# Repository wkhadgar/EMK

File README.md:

# EMK
EDGE Macro Keyboard using ZMK

# BOM
Link 1: https://docs.google.com/spreadsheets/d/1feDPUKi6qvB3Wog3a3WXaTfP1I-IvefD0QiZMtcDikI/edit?usp=sharing

Link 2: https://docs.google.com/spreadsheets/d/19HNuX7kSN2P8mtOWgADNLb8_vFuXl1ejLlQBJqbNmKw/edit?gid=1410846494#gid=1410846494

# Block Diagram:

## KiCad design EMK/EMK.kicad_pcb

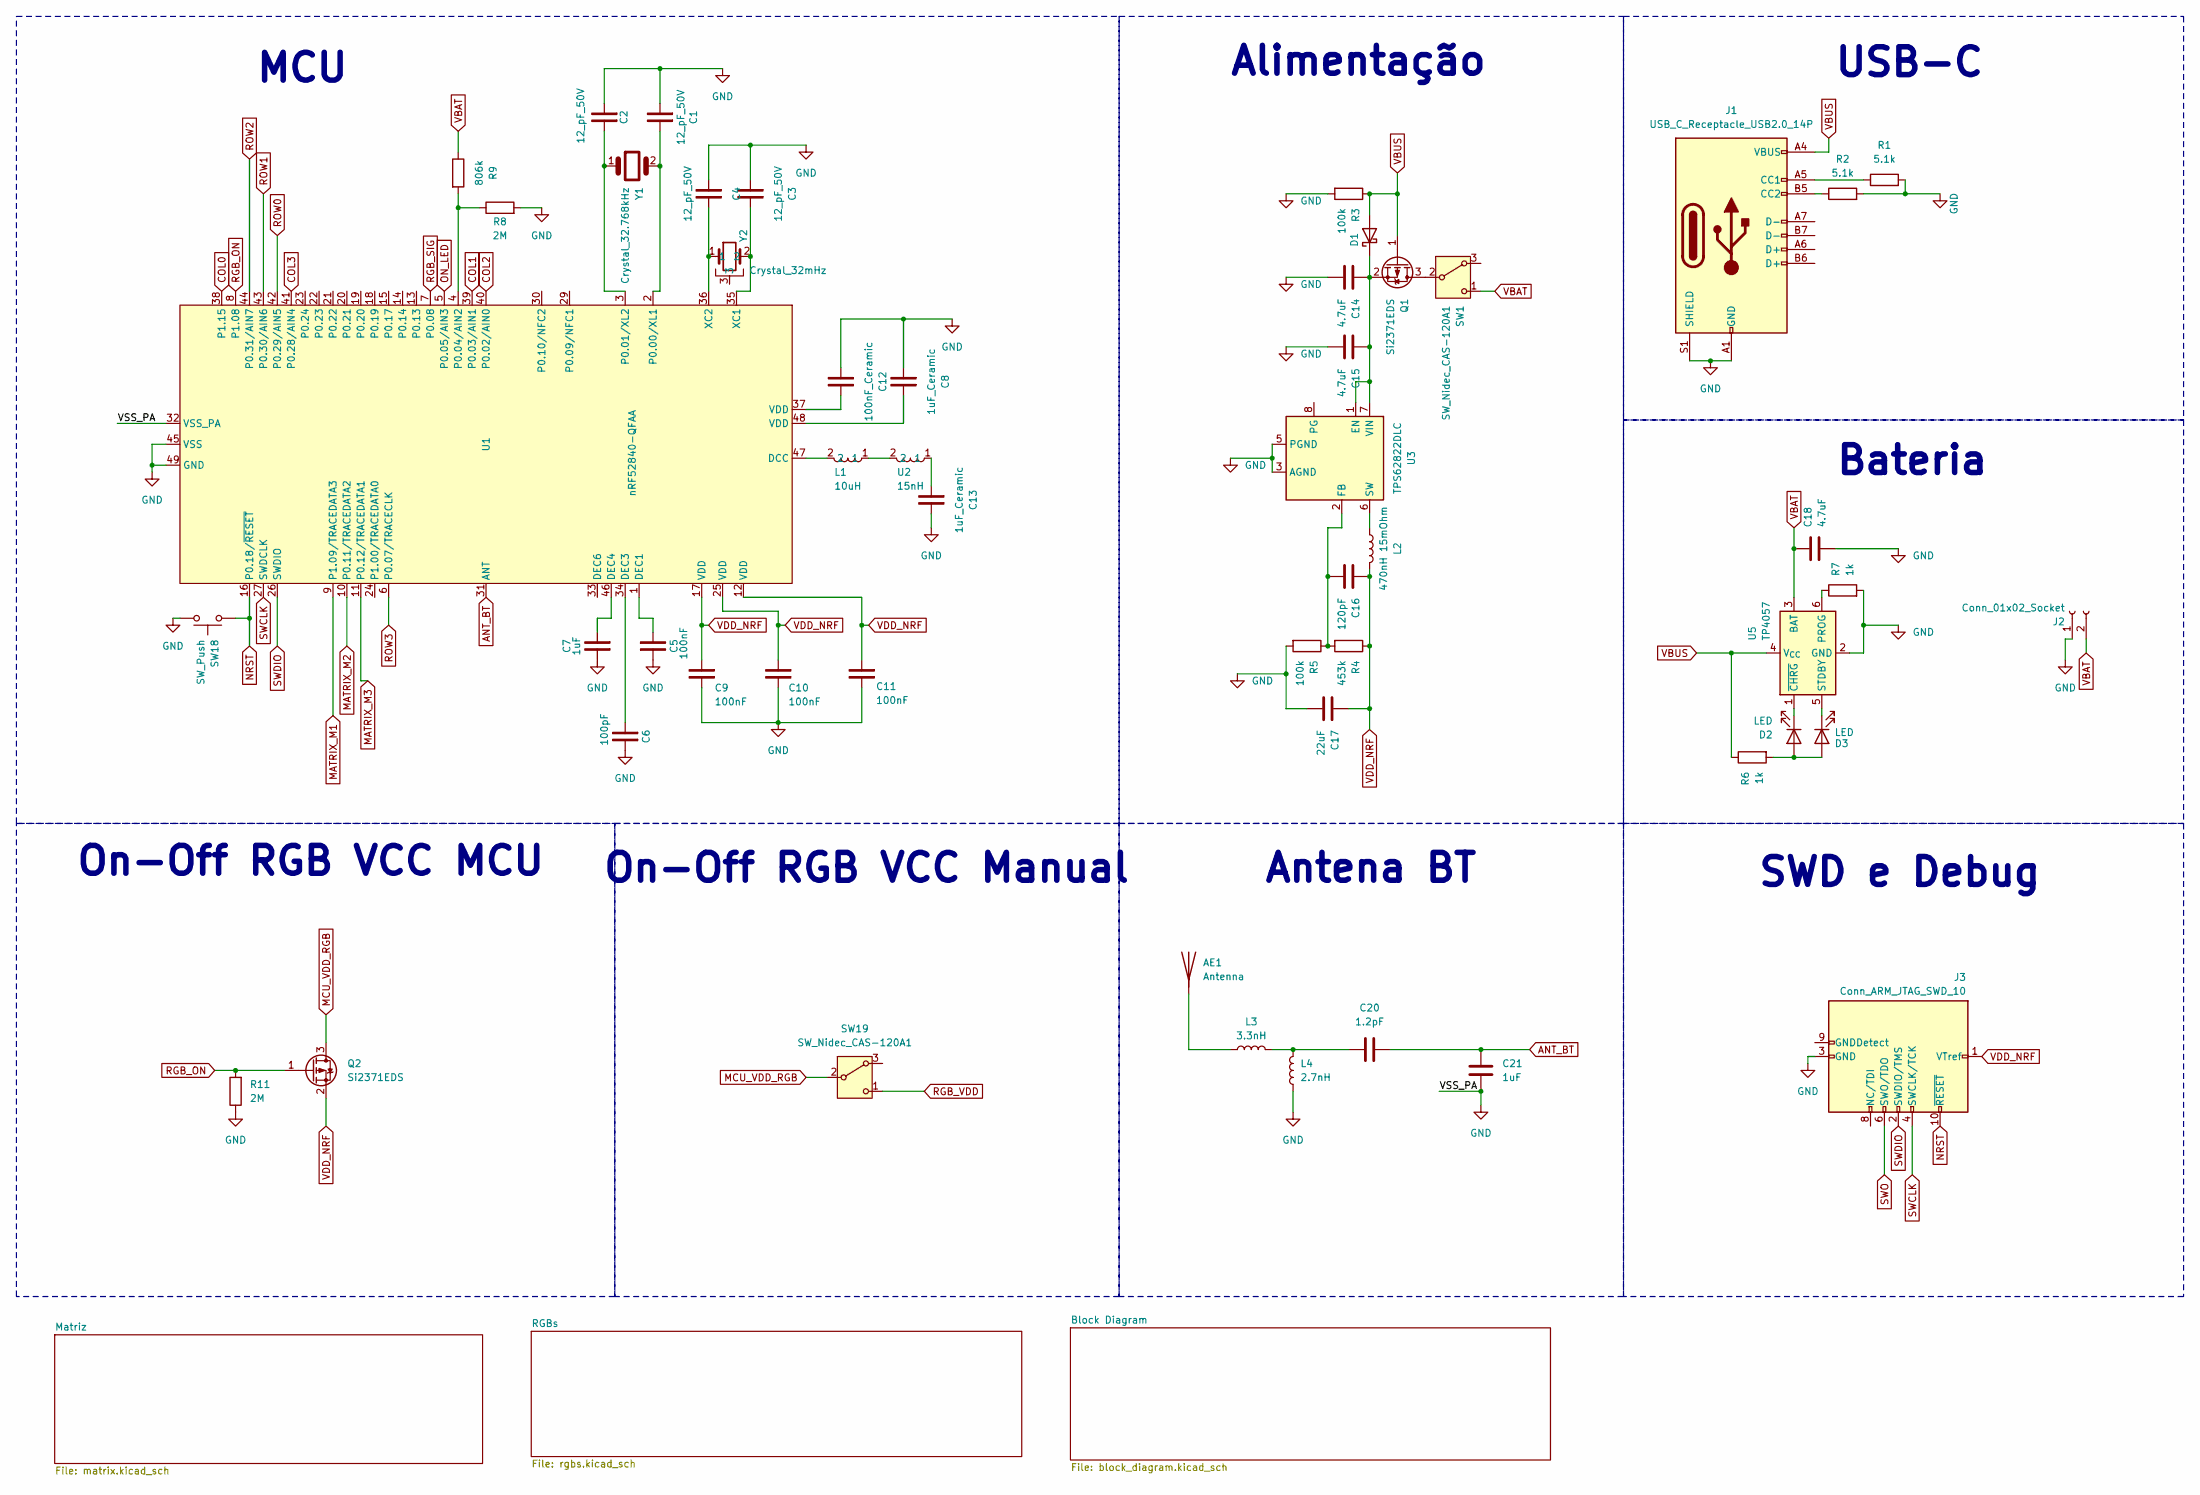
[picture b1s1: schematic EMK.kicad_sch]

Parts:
AE1: Antenna; Johanson_2450AT18x100
C1, C2, C3, C4: 12_pF_50V; C_0603_1608Metric
C5, C9, C10, C11: 100nF; C_0603_1608Metric
C6: 100pF; C_0603_1608Metric
C7: 1uF; C_0402_1005Metric
C8, C13: 1uF_Ceramic; C_0603_1608Metric
C12: 100nF_Ceramic; C_0603_1608Metric
C14, C15, C18: 4.7uF; C_0603_1608Metric
C16: 120pF; C_0603_1608Metric
C17: 22uF; C_0603_1608Metric
C20: 1.2pF; C_0402_1005Metric
C21: 1uF; C_0603_1608Metric
D1: D_Schottky; D_0805_2012Metric
D2, D3: LED; LED_0603_1608Metric
J1: USB_C_Receptacle_USB2.0_14P; USB_C_Receptacle_XKB_U262-16XN-4BVC11
J2: Conn_01x02_Socket; PinHeader_1x02_P2.54mm_Horizontal
J3: Conn_ARM_JTAG_SWD_10; ARM_SWD_SMD_TH
L1: 10uH; L_0603_1608Metric
L2: 470nH 15mOhm; L_7.3x7.3_H4.5
L3: 3.3nH; L_0402_1005Metric
L4: 2.7nH; L_0402_1005Metric_Pad0.77x0.64mm_HandSolder
Q1, Q2: Si2371EDS; SOT-23
R1, R2: 5.1k; R_0603_1608Metric
R3, R5: 100k; R_0603_1608Metric
R4: 453k; R_0603_1608Metric
R6, R7: 1k; R_0603_1608Metric
R8: 2M; R_0603_1608Metric
R9: 806k; R_0603_1608Metric
R11: 2M; R_0402_1005Metric
SW1, SW19: SW_Nidec_CAS-120A1; Nidec_Copal_CAS-120A
SW18: SW_Push; SW_SPST_B3U-1000P
U1: nRF52840-QFAA; QFN-48-1EP_6x6mm_P0.4mm_EP4.6x4.6mm
U2: 15nH; L_0603_1608Metric
U3: TPS62822DLC; Texas_VSON-HR-8_1.5x2mm_P0.5mm
U5: TP4057; TSOT-23-6
Y1: Crystal_32.768kHz; Crystal_SMD_2012-2Pin_2.0x1.2mm
Y2: Crystal_32mHz; Crystal_SMD_3215-2Pin_3.2x1.5mm

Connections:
ANT_BT: C20.2, C21.1, U1.31 (ANT)
COL0: U1.38 (P1.15); also elsewhere on the board
COL1: U1.39 (P0.03/AIN1); also elsewhere on the board
COL2: U1.40 (P0.02/AIN0); also elsewhere on the board
COL3: U1.41 (P0.28/AIN4); also elsewhere on the board
GND: C1.1, C2.1, C3.1, C4.1, C5.1, C6.2, C7.2, C8.1, C9.2, C10.2, C11.2, C12.1, C13.2, C14.2, C15.2, C17.2, C18.2, C21.2, J1.A1 (GND), J1.A12 (GND), J1.B1 (GND), J1.B12 (GND), J1.S1 (SHIELD), J2.1, J3.3 (GND), J3.5 (GND), L4.1, R1.2, R2.2, R3.2, R5.2, R7.2, R8.2, R11.1, SW18.2, U1.32 (VSS_PA), U1.45 (VSS), U1.49 (GND), U3.3 (AGND), U3.5 (PGND), U5.2 (GND); also elsewhere on the board
MATRIX_M1: U1.9 (P1.09/TRACEDATA3); also elsewhere on the board
MATRIX_M2: U1.10 (P0.11/TRACEDATA2); also elsewhere on the board
MATRIX_M3: U1.11 (P0.12/TRACEDATA1); also elsewhere on the board
MCU_VDD_RGB: Q2.3 (D), SW19.2 (B)
NRST: J3.10 (~RESET), SW18.1, U1.16 (P0.18/~RESET)
unnamed: AE1.1 (A), L3.1
unnamed: C8.2, U1.48 (VDD)
unnamed: C12.2, U1.37 (VDD)
unnamed: C13.1, U2.1
unnamed: C20.1, L3.2, L4.2
unnamed: C14.1, C15.1, D1.1 (K), Q1.2 (S), U3.1 (EN), U3.7 (VIN)
unnamed: D2.2 (A), D3.2 (A), R6.2
unnamed: D2.1 (K), U5.1 (~CHRG)
unnamed: D3.1 (K), U5.5 (STDBY)
unnamed: J1.A5 (CC1), R1.1
unnamed: J1.B5 (CC2), R2.1
unnamed: L1.1, U2.2
unnamed: Q1.3 (D), SW1.2 (B)
unnamed: L1.2, U1.47 (DCC)
unnamed: C5.2, U1.1 (DEC1)
unnamed: C6.1, U1.34 (DEC3)
unnamed: C7.1, U1.46 (DEC4)
unnamed: C1.2, U1.2 (P0.00/XL1), Y1.2
unnamed: C2.2, U1.3 (P0.01/XL2), Y1.1
unnamed: R8.1, R9.2, U1.4 (P0.04/AIN2)
unnamed: C3.2, U1.35 (XC1), Y2.2
unnamed: C4.2, U1.36 (XC2), Y2.1
unnamed: C16.2, R4.2, R5.1, U3.2 (FB)
unnamed: L2.1, U3.6 (SW)
unnamed: R7.1, U5.6 (PROG)
ON_LED: U1.5 (P0.05/AIN3); also elsewhere on the board
RGB_ON: Q2.1 (G), R11.2, U1.8 (P1.08)
RGB_SIG: U1.7 (P0.08); also elsewhere on the board
RGB_VDD: SW19.1 (C); also elsewhere on the board
ROW0: U1.42 (P0.29/AIN5); also elsewhere on the board
ROW1: U1.43 (P0.30/AIN6); also elsewhere on the board
ROW2: U1.44 (P0.31/AIN7); also elsewhere on the board
ROW3: U1.6 (P0.07/TRACECLK); also elsewhere on the board
SWCLK: J3.4 (SWCLK/TCK), U1.27 (SWDCLK)
SWDIO: J3.2 (SWDIO/TMS), U1.26 (SWDIO)
SWO: J3.6 (SWO/TDO)
VBAT: C18.1, J2.2, R9.1, SW1.1 (C), U5.3 (BAT)
VBUS: D1.2 (A), J1.A4 (VBUS), J1.A9 (VBUS), J1.B4 (VBUS), J1.B9 (VBUS), Q1.1 (G), R3.1, R6.1, U5.4 (V_{CC})
VDD_NRF: C9.1, C10.1, C11.1, C16.1, C17.1, J3.1 (VTref), L2.2, Q2.2 (S), R4.1, U1.12 (VDD), U1.17 (VDD), U1.25 (VDD); also elsewhere on the board

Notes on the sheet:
Alimentação
Bateria
SWD e Debug
MCU
Antena BT
On-Off RGB VCC MCU
On-Off RGB VCC Manual
USB-C

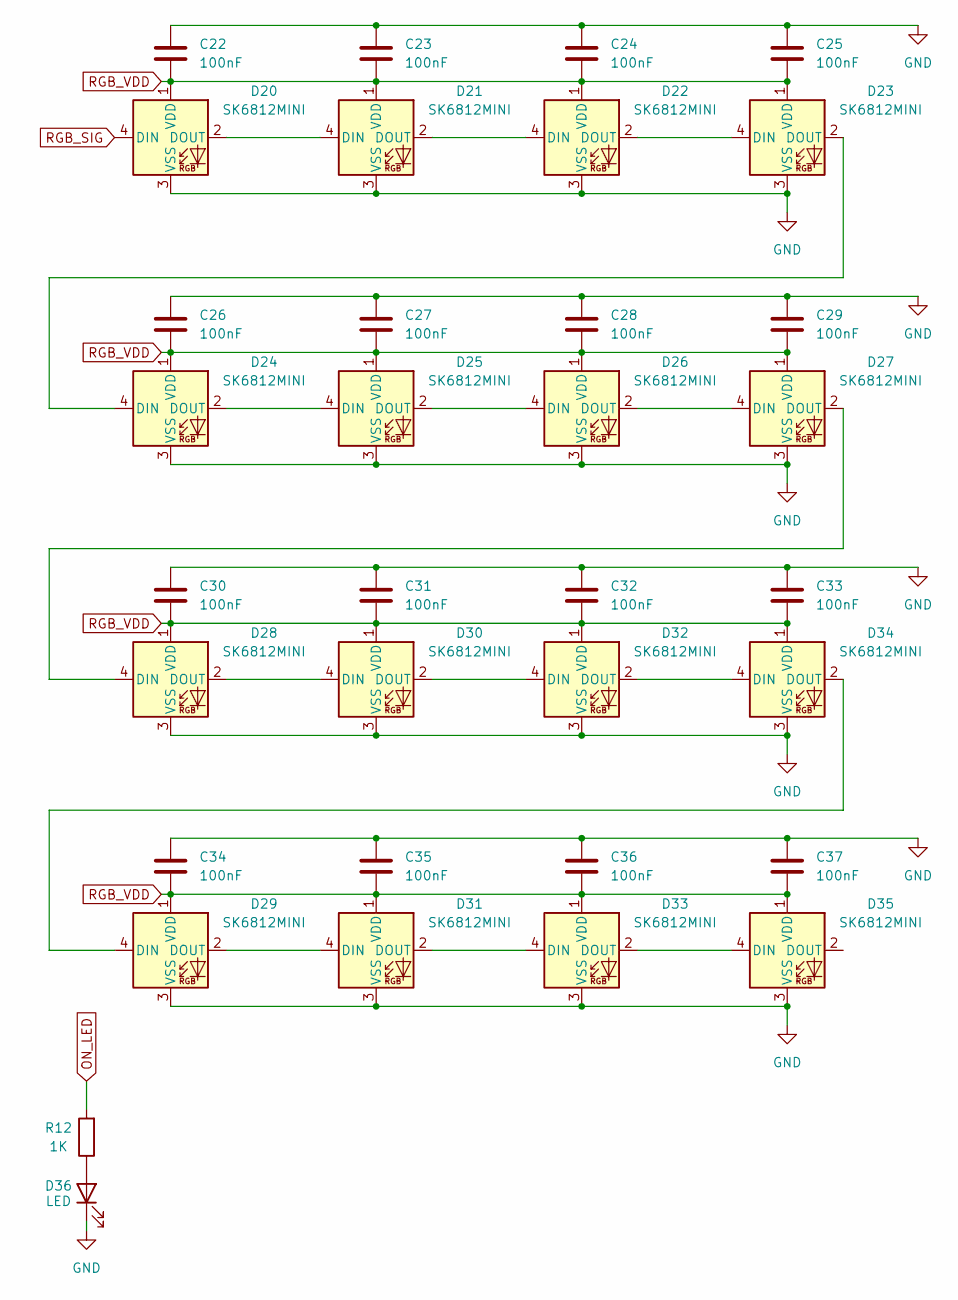
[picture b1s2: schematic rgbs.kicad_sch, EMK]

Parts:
C22, C23, C24, C25, C26, C27, C28, C29, C30, C31, C32, C33, C34, C35, C36, C37: 100nF; C_0603_1608Metric
D20, D21, D22, D23, D24, D25, D26, D27, D28, D29, D30, D31, D32, D33, D34, D35: SK6812MINI; SK6812MINI-E-PLCC4_3.2x2.8mm
D36: LED; LED_0603_1608Metric
R12: 1K; R_0603_1608Metric

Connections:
GND: C22.1, C23.1, C24.1, C25.1, C26.1, C27.1, C28.1, C29.1, C30.1, C31.1, C32.1, C33.1, C34.1, C35.1, C36.1, C37.1, D20.3 (VSS), D21.3 (VSS), D22.3 (VSS), D23.3 (VSS), D24.3 (VSS), D25.3 (VSS), D26.3 (VSS), D27.3 (VSS), D28.3 (VSS), D29.3 (VSS), D30.3 (VSS), D31.3 (VSS), D32.3 (VSS), D33.3 (VSS), D34.3 (VSS), D35.3 (VSS), D36.1 (K); also elsewhere on the board
unnamed: D20.2 (DOUT), D21.4 (DIN)
unnamed: D21.2 (DOUT), D22.4 (DIN)
unnamed: D22.2 (DOUT), D23.4 (DIN)
unnamed: D23.2 (DOUT), D24.4 (DIN)
unnamed: D24.2 (DOUT), D25.4 (DIN)
unnamed: D25.2 (DOUT), D26.4 (DIN)
unnamed: D26.2 (DOUT), D27.4 (DIN)
unnamed: D27.2 (DOUT), D28.4 (DIN)
unnamed: D28.2 (DOUT), D30.4 (DIN)
unnamed: D29.4 (DIN), D34.2 (DOUT)
unnamed: D29.2 (DOUT), D31.4 (DIN)
unnamed: D30.2 (DOUT), D32.4 (DIN)
unnamed: D31.2 (DOUT), D33.4 (DIN)
unnamed: D32.2 (DOUT), D34.4 (DIN)
unnamed: D33.2 (DOUT), D35.4 (DIN)
unnamed: D36.2 (A), R12.1
ON_LED: R12.2; also elsewhere on the board
RGB_SIG: D20.4 (DIN); also elsewhere on the board
RGB_VDD: C22.2, C23.2, C24.2, C25.2, C26.2, C27.2, C28.2, C29.2, C30.2, C31.2, C32.2, C33.2, C34.2, C35.2, C36.2, C37.2, D20.1 (VDD), D21.1 (VDD), D22.1 (VDD), D23.1 (VDD), D24.1 (VDD), D25.1 (VDD), D26.1 (VDD), D27.1 (VDD), D28.1 (VDD), D29.1 (VDD), D30.1 (VDD), D31.1 (VDD), D32.1 (VDD), D33.1 (VDD), D34.1 (VDD), D35.1 (VDD); also elsewhere on the board

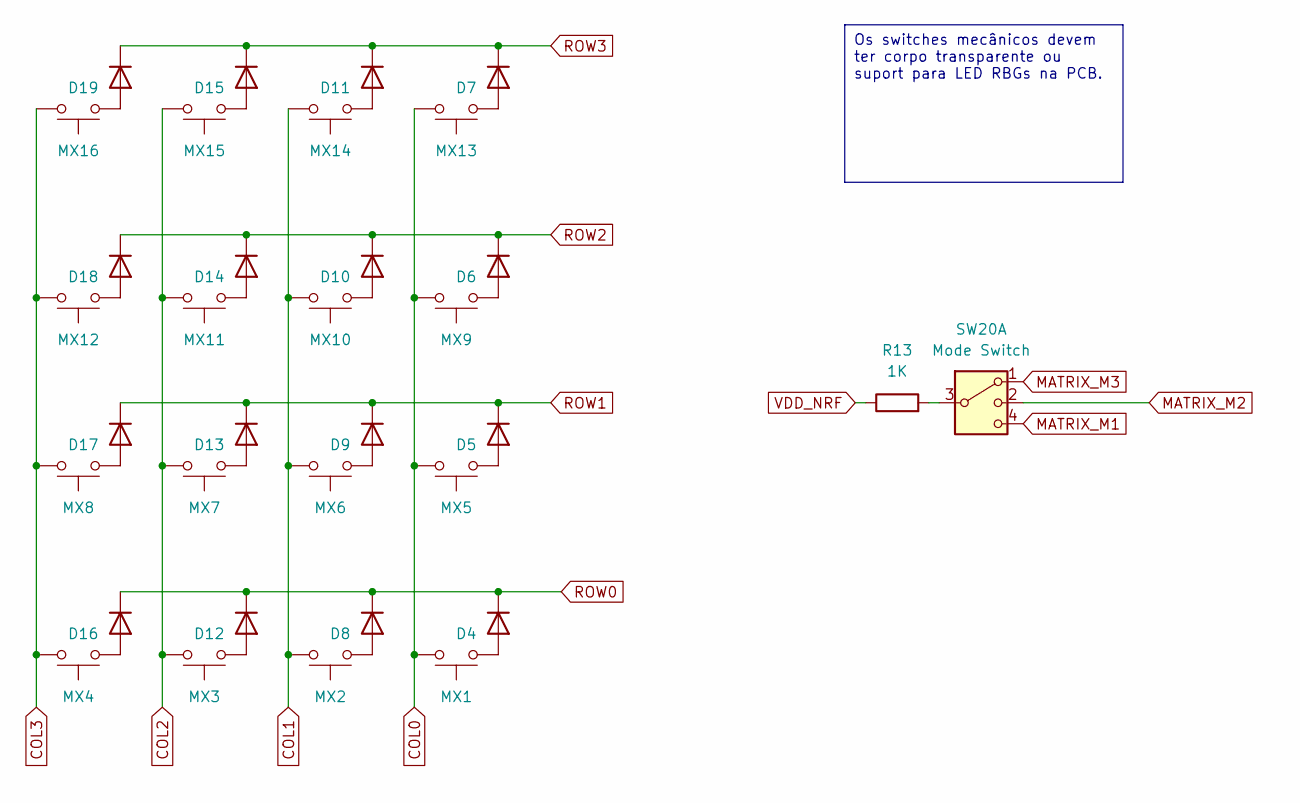
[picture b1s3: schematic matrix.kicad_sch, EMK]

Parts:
D4, D5, D6, D7, D8, D9, D10, D11, D12, D13, D14, D15, D16, D17, D18, D19: D; D_0603_1608Metric
R13: 1K; R_0603_1608Metric
SW2: MX1; SW_Cherry_MX_1.25u_PCB
SW3: MX5; SW_Cherry_MX_1.50u_PCB
SW4: MX9; SW_Cherry_MX_1.50u_PCB
SW5: MX13; SW_Cherry_MX_1.00u_Plate
SW6: MX2; SW_Cherry_MX_1.25u_PCB
SW7: MX6; SW_Cherry_MX_1.50u_PCB
SW8: MX10; SW_Cherry_MX_1.50u_PCB
SW9: MX14; SW_Cherry_MX_1.00u_Plate
SW10: MX3; SW_Cherry_MX_1.25u_PCB
SW11: MX7; SW_Cherry_MX_1.00u_Plate
SW12: MX11; SW_Cherry_MX_1.00u_Plate
SW13: MX15; SW_Cherry_MX_1.00u_Plate
SW14: MX4; SW_Cherry_MX_1.25u_PCB
SW15: MX8; SW_Cherry_MX_1.00u_Plate
SW16: MX12; SW_Cherry_MX_1.00u_Plate
SW17: MX16; SW_Cherry_MX_1.00u_Plate
SW20: Mode Switch; MODE-SWITCH-SLW12745474ARAD

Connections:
COL0: SW2.2, SW3.2, SW4.2, SW5.2; also elsewhere on the board
COL1: SW6.2, SW7.2, SW8.2, SW9.2; also elsewhere on the board
COL2: SW10.2, SW11.2, SW12.2, SW13.2; also elsewhere on the board
COL3: SW14.2, SW15.2, SW16.2, SW17.2; also elsewhere on the board
MATRIX_M1: SW20.4; also elsewhere on the board
MATRIX_M2: SW20.2; also elsewhere on the board
MATRIX_M3: SW20.1; also elsewhere on the board
unnamed: D4.2 (A), SW2.1
unnamed: D5.2 (A), SW3.1
unnamed: D6.2 (A), SW4.1
unnamed: D7.2 (A), SW5.1
unnamed: D8.2 (A), SW6.1
unnamed: D9.2 (A), SW7.1
unnamed: D10.2 (A), SW8.1
unnamed: D11.2 (A), SW9.1
unnamed: D12.2 (A), SW10.1
unnamed: D13.2 (A), SW11.1
unnamed: D14.2 (A), SW12.1
unnamed: D15.2 (A), SW13.1
unnamed: D16.2 (A), SW14.1
unnamed: D17.2 (A), SW15.1
unnamed: D18.2 (A), SW16.1
unnamed: D19.2 (A), SW17.1
unnamed: R13.2, SW20.3
ROW0: D4.1 (K), D8.1 (K), D12.1 (K), D16.1 (K); also elsewhere on the board
ROW1: D5.1 (K), D9.1 (K), D13.1 (K), D17.1 (K); also elsewhere on the board
ROW2: D6.1 (K), D10.1 (K), D14.1 (K), D18.1 (K); also elsewhere on the board
ROW3: D7.1 (K), D11.1 (K), D15.1 (K), D19.1 (K); also elsewhere on the board
VDD_NRF: R13.1; also elsewhere on the board

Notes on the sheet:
Os switches mecânicos devem ter corpo transparente ou suport para LED RBGs na PCB.

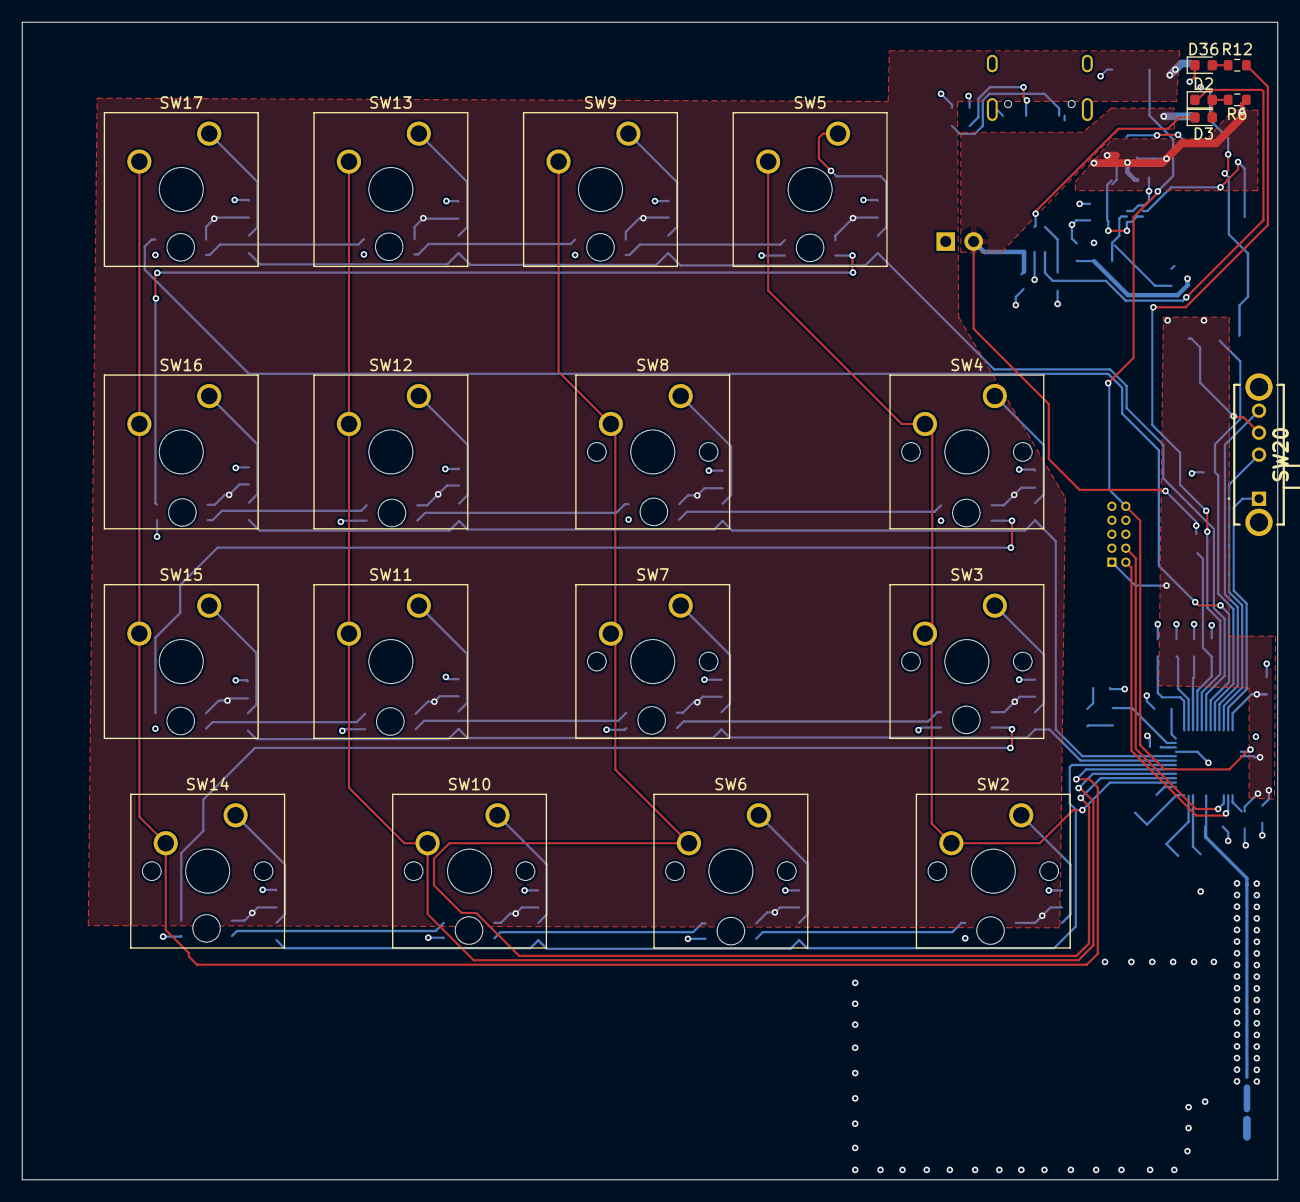
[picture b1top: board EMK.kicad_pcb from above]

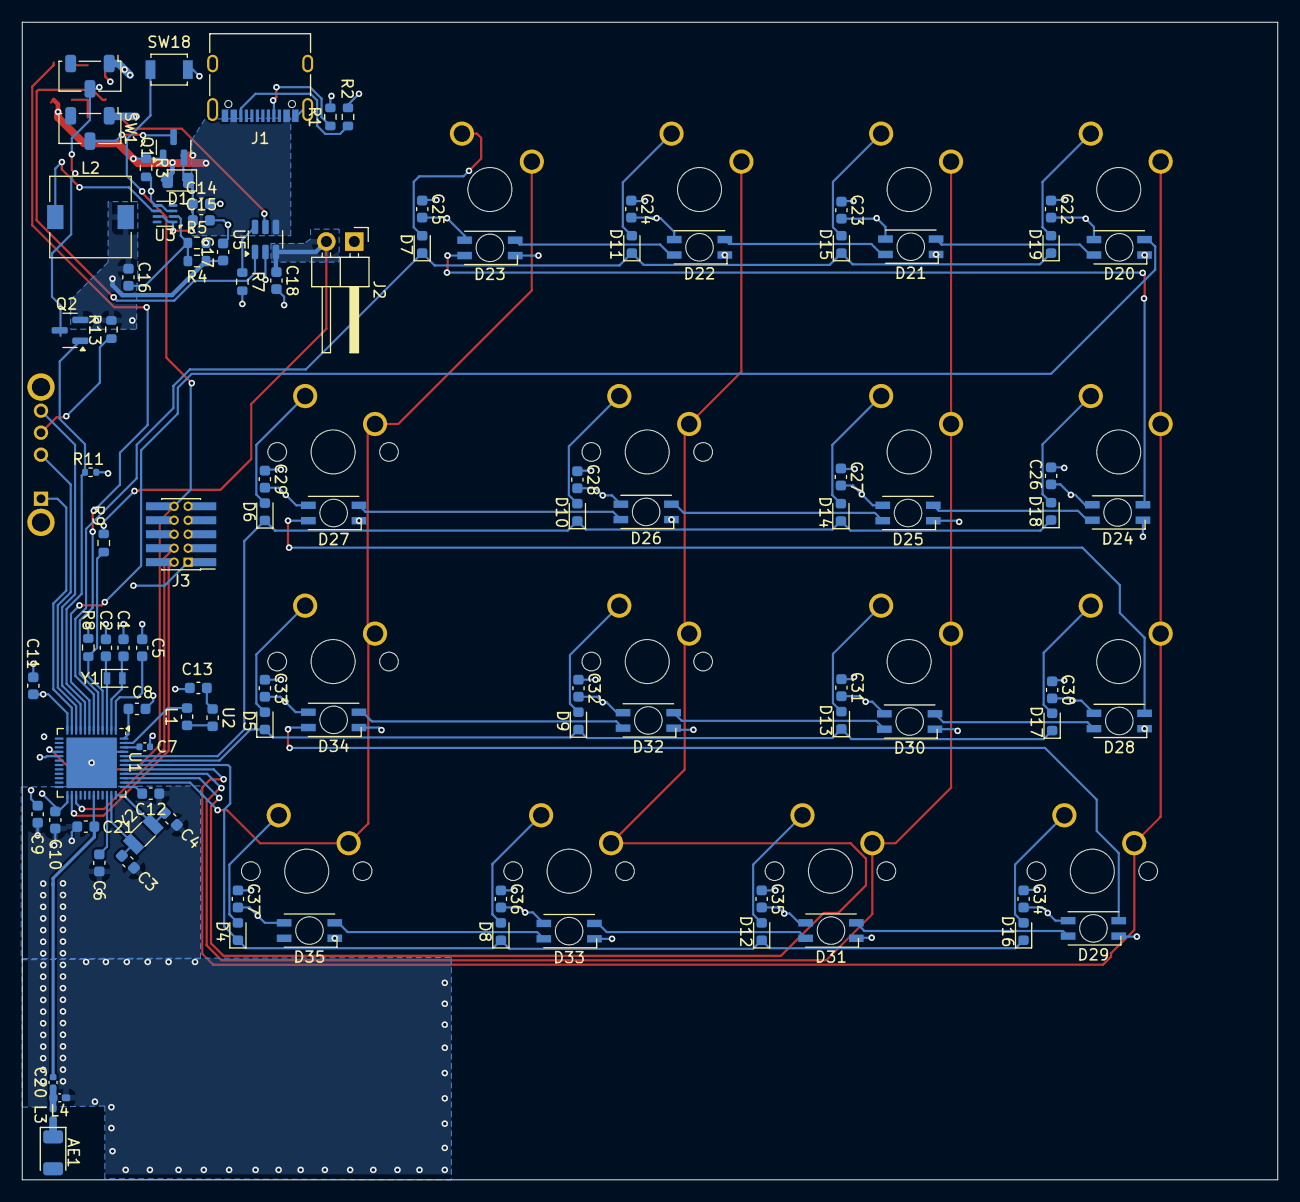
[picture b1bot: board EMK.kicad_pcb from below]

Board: 4 copper layers, 114.1 x 105.2 mm, 120 parts (98 on the bottom side), 82 nets.

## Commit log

2024-09-28 Adição do projeto do KiCad
2024-10-10 Update README.md
    Update readme with BOM link and Blocks Diagram
2024-10-10 Adiciona a biblioteca dos switches
    Adiciona a biblioteca com os switches do teclado.
2024-10-10 Adição da MCU nRF52840
2024-10-10 Alimentação NRF
2024-10-10 SWD NRF
2024-10-10 feat: cria a lib de energia
2024-10-10 feat: adiciona o power management
2024-10-10 wip: Introduz a matriz de botões ao esquemático.
2024-10-10 feat: adiciona a matriz de switches.
2024-10-10 feat: adiciona o conector SWD.
2024-10-11 feat: organiza o esquemático e adiciona as labels aos blocos.
2024-10-11 feat: adiciona o controle de alimentação dos RGBs.
2024-10-11 feat: conclui a revisão 1 do EMK.
2024-10-30 Adiciona parte dos Footprints
2024-10-31 Roteamento da MCU e posicionamento
2024-10-31 feat: realiza o roteamento das trilhas da matriz e dos leds.
2024-10-31 Roteamento
2024-11-01 feat: Adiciona os componentes faltantes.
2024-11-05 Adiciona os componentes faltantes na PCI.
2024-11-06 Ajusta a PCI
    Adiciona as trilhas faltantes.
2024-11-12 Alimentação
2024-11-12 Alimentação - Fix
2024-11-14 Finalização
2024-11-20 Remap tracement
2024-11-21 Refatora a antena
    Ajusta a antena.
2024-11-21 Impendancia de 50 Ohnms
2024-11-29 Corrige problemas de vias
